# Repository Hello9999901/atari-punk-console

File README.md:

Quick attempt at making an atari punk console.

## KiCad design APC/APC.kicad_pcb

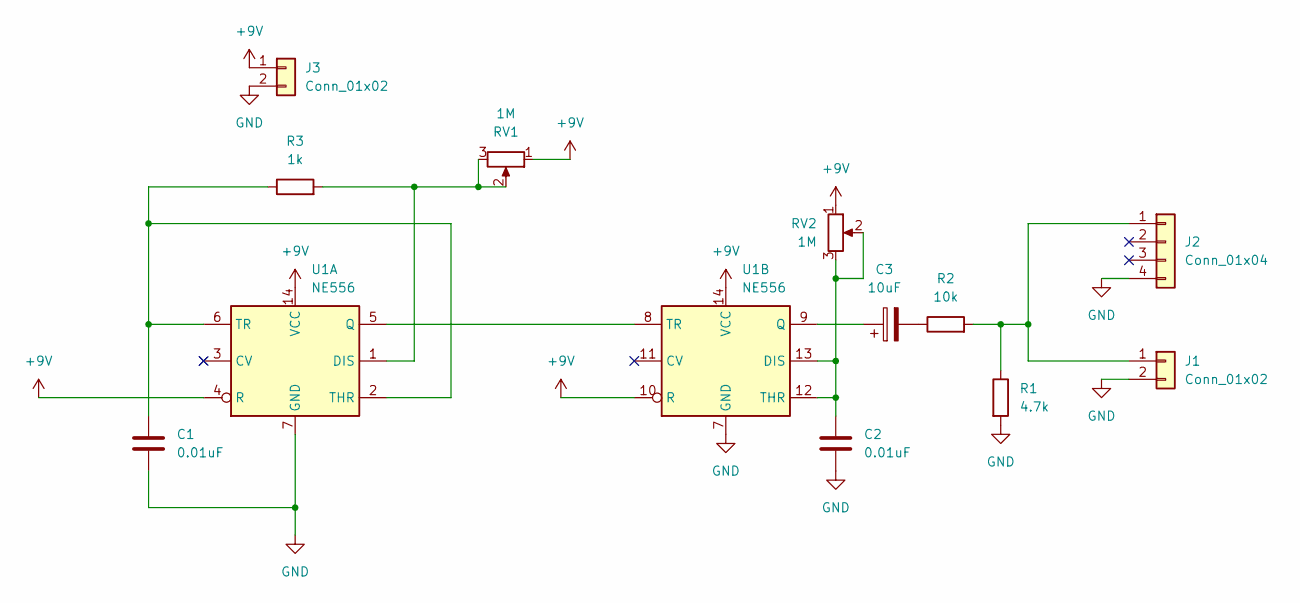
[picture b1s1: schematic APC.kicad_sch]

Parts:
C1, C2: 0.01uF; C_Disc_D4.3mm_W1.9mm_P5.00mm
C3: 10uF; CP_Radial_D5.0mm_P2.50mm
J1, J3: Conn_01x02; TerminalBlock_MaiXu_MX126-5.0-02P_1x02_P5.00mm
J2: Conn_01x04; PinHeader_1x04_P2.54mm_Vertical
R1: 4.7k; R_Axial_DIN0207_L6.3mm_D2.5mm_P10.16mm_Horizontal
R2: 10k; R_Axial_DIN0207_L6.3mm_D2.5mm_P10.16mm_Horizontal
R3: 1k; R_Axial_DIN0207_L6.3mm_D2.5mm_P10.16mm_Horizontal
RV1, RV2: 1M; Potentiometer_Alps_RK163_Single_Horizontal
U1: NE556; DIP-14_W7.62mm_Socket_LongPads

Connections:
+9V: J3.1, RV1.1, RV2.1, U1.4 (R), U1.10 (R), U1.14 (VCC)
GND: C1.2, C2.2, J1.2, J2.4, J3.2, R1.2, U1.7 (GND)
unnamed: C3.2, R2.1
unnamed: J1.1, J2.1, R1.1, R2.2
unnamed: R3.2, RV1.2, RV1.3, U1.1 (DIS)
unnamed: U1.5 (Q), U1.8 (TR)
unnamed: C1.1, R3.1, U1.2 (THR), U1.6 (TR)
unnamed: C2.1, RV2.2, RV2.3, U1.12 (THR), U1.13 (DIS)
unnamed: C3.1, U1.9 (Q)

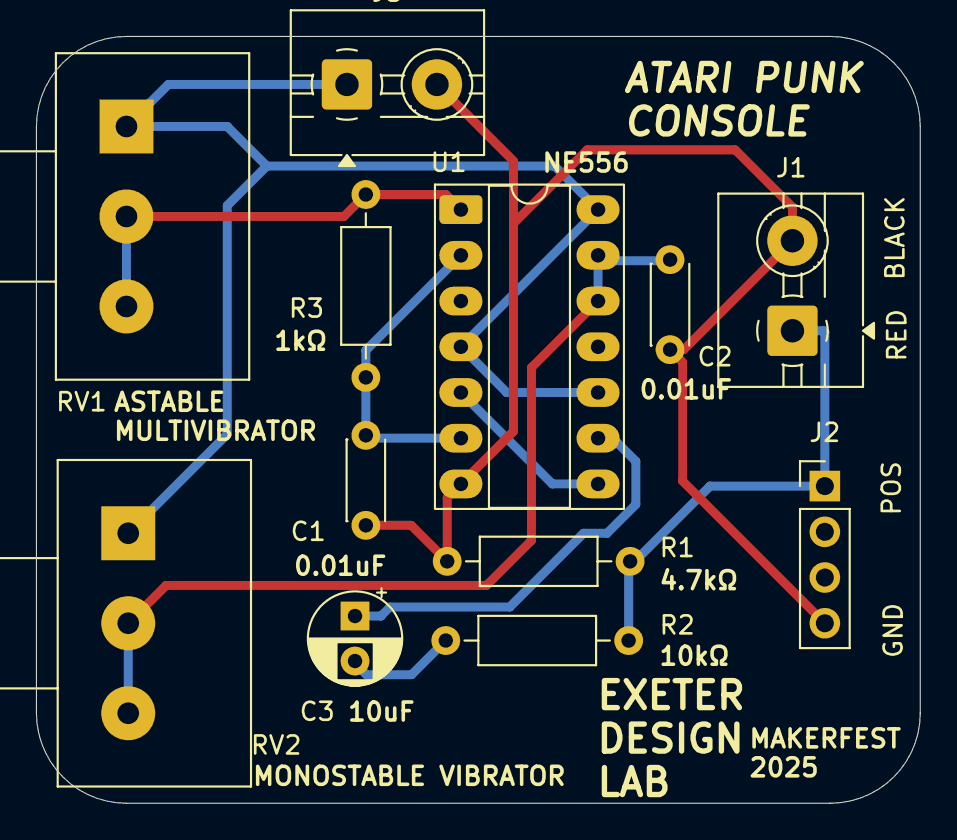
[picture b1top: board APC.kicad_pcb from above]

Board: 2 copper layers, 49.1 x 42.6 mm, 12 parts (0 on the bottom side), 9 nets.
